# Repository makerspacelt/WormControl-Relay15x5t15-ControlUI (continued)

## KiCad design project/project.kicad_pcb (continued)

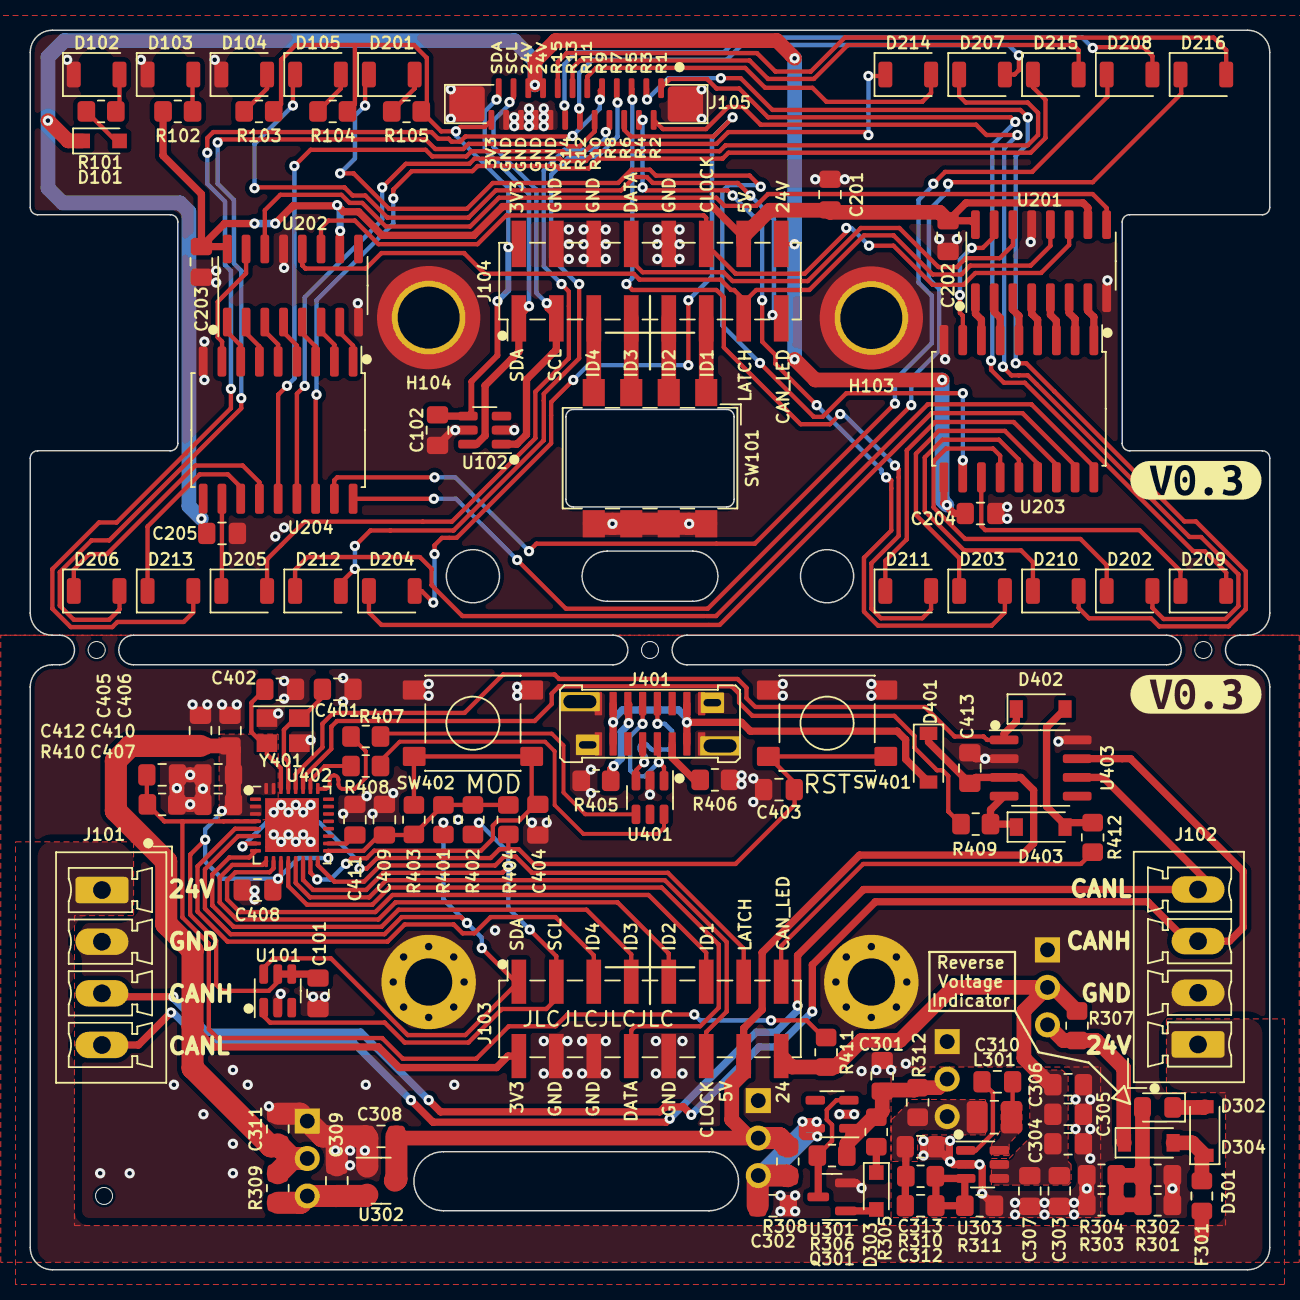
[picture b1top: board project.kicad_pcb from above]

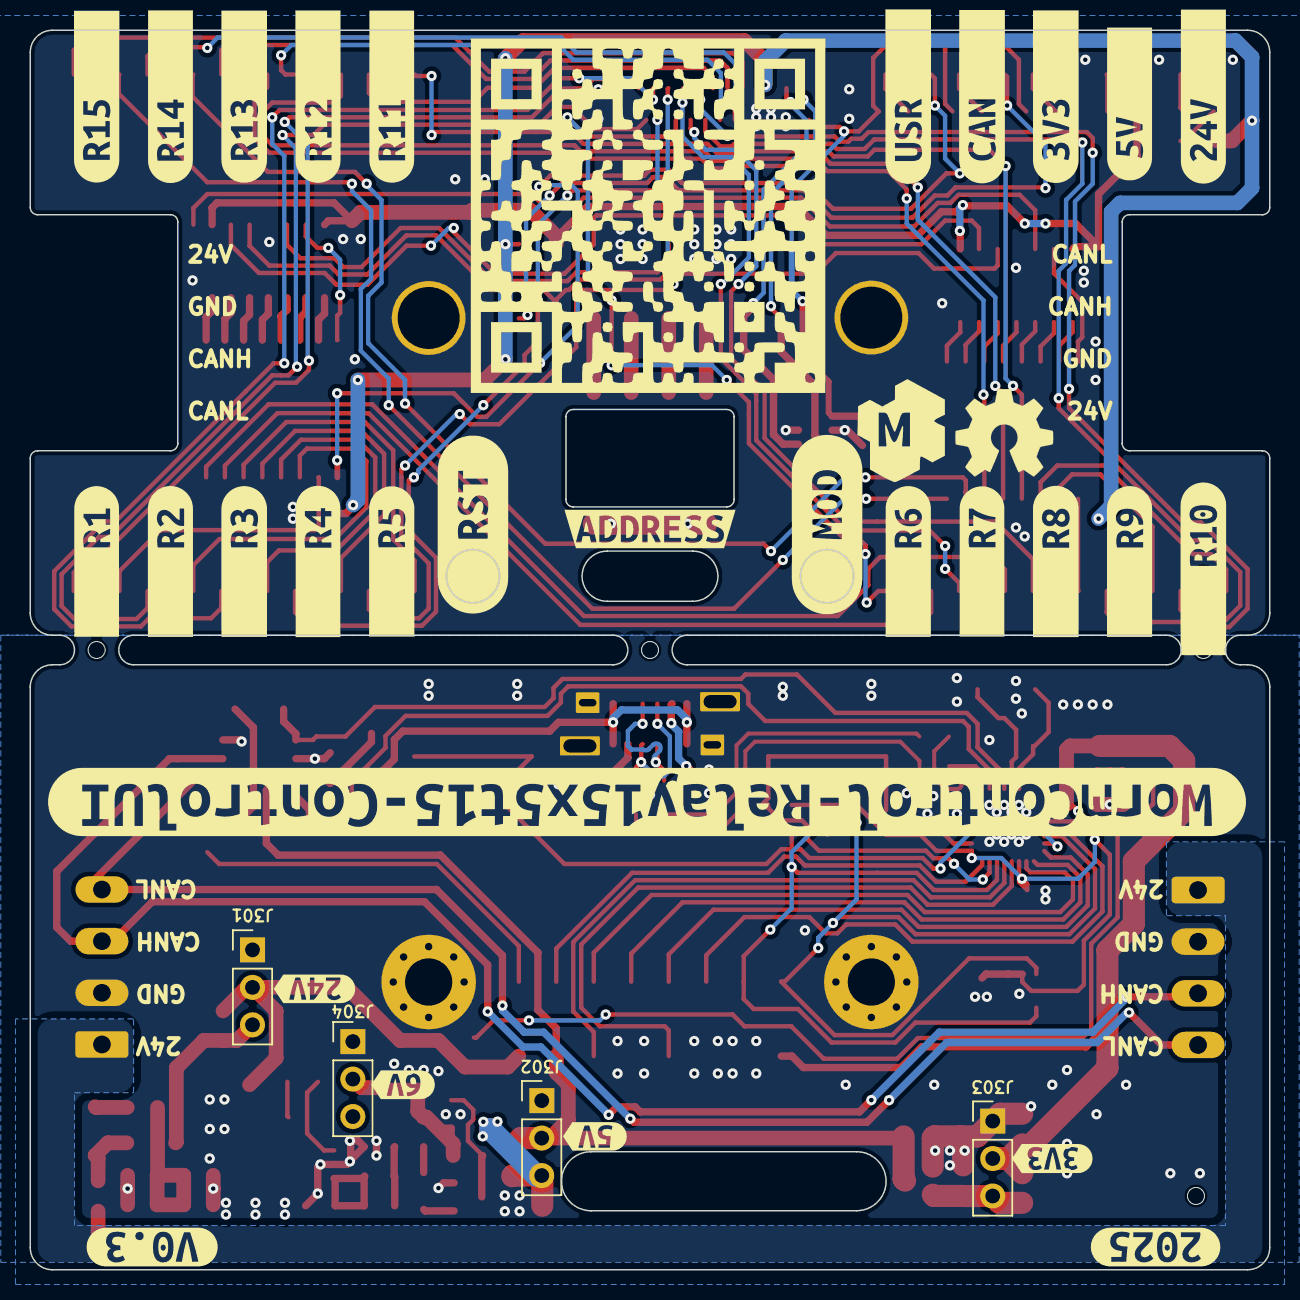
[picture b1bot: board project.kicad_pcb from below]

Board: 4 copper layers, 84.0 x 84.0 mm, 157 parts (36 on the bottom side), 118 nets.

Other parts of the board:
kibuzzard-68F6C7D9: G***; kibuzzard-68F6C7D9
kibuzzard-68F6C8CD: G***; kibuzzard-68F6C8CD
kibuzzard-68F6C9D1: G***; kibuzzard-68F6C9D1
kibuzzard-68F6C9D9: G***; kibuzzard-68F6C9D9
kibuzzard-68F6C81E: G***; kibuzzard-68F6C81E
kibuzzard-68F6C83B: G***; kibuzzard-68F6C83B
kibuzzard-68F6C776: G***; kibuzzard-68F6C776
kibuzzard-68F6C793: G***; kibuzzard-68F6C793
kibuzzard-67993A27: G***; kibuzzard-67993A27
kibuzzard-679934A0: G***; kibuzzard-679934A0
kibuzzard-679934B0: G***; kibuzzard-679934B0
kibuzzard-679934DC: G***; kibuzzard-679934DC
kibuzzard-679934EA: G***; kibuzzard-679934EA
kibuzzard-679935A9: G***; kibuzzard-679935A9
kibuzzard-679935B4: G***; kibuzzard-679935B4
kibuzzard-679935C1: G***; kibuzzard-679935C1
kibuzzard-6799352B: G***; kibuzzard-6799352B
kibuzzard-6799357E: G***; kibuzzard-6799357E
kibuzzard-6799359C: G***; kibuzzard-6799359C
kibuzzard-6799365E: G***; kibuzzard-6799365E
kibuzzard-67993413: G***; kibuzzard-67993413
kibuzzard-67993427: G***; kibuzzard-67993427
kibuzzard-67993436: G***; kibuzzard-67993436
kibuzzard-67993449: G***; kibuzzard-67993449
kibuzzard-67993459: G***; kibuzzard-67993459
kibuzzard-67993507: G***; kibuzzard-67993507
kibuzzard-67993514: G***; kibuzzard-67993514
kibuzzard-67993518: G***; kibuzzard-67993518
kibuzzard-67993537: G***; kibuzzard-67993537
kibuzzard-67993543: G***; kibuzzard-67993543
kibuzzard-67993570: G***; kibuzzard-67993570
kibuzzard-67993590: G***; kibuzzard-67993590

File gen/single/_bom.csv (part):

"Row","Description","Part","References","Value","Footprint","Quantity Per PCB","Status","Datasheet","lcsc#","jlc-part-type","alt#"
"1","Heatsink","Heatsink","BOM101,BOM102","1x4 screw plug","","2"," ","https://www.lcsc.com/datasheet/lcsc_datasheet_2309070925_DEG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","C7603442","E",""
"2","Unpolarized capacitor","C","C401,C402","10p","C_0805_2012Metric_Pad1.18x1.45mm_HandSolder","2"," ","https://www.lcsc.com/datasheet/lcsc_datasheet_2304140030_Sam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","C1634","B",""
"3","Unpolarized capacitor","C","C312","100p","C_0805_2012Metric_Pad1.18x1.45mm_HandSolder","1"," ","https://www.lcsc.com/datasheet/lcsc_datasheet_2304140030_Sam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","C1790","B",""
"4","Unpolarized capacitor","C","C101,C102,C202,C203,C307,C310,C403,C404,C407,C408,C409,C410,C411,C412,C413","100n","C_0805_2012Metric_Pad1.18x1.45mm_HandSolder","15"," ","https://www.lcsc.com/datasheet/lcsc_datasheet_2304140030_Sam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","C28233","B",""
"5","Unpolarized capacitor","C","C406","1u","C_0805_2012Metric_Pad1.18x1.45mm_HandSolder","1"," ","https://www.lcsc.com/datasheet/lcsc_datasheet_2304140030_Sam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","C28323","B",""
"6","Unpolarized capacitor","C","C204,C205,C301,C303,C304,C305,C306,C313","10u/50v","C_0805_2012Metric_Pad1.18x1.45mm_HandSolder","8"," ","https://www.lcsc.com/datasheet/lcsc_datasheet_2411041759_Mur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","C440198","B",""
"7","Unpolarized capacitor","C","C201,C302,C308,C405","22u/25v","C_0805_2012Metric_Pad1.18x1.45mm_HandSolder","4"," ","https://www.lcsc.com/datasheet/lcsc_datasheet_2304140030_Sam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","C45783","B",""
"8","Unpolarized capacitor","C","C309,C311","47u/6V3","C_0805_2012Metric_Pad1.18x1.45mm_HandSolder","2"," ","https://www.lcsc.com/datasheet/lcsc_datasheet_2304140030_Sam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","C16780","B",""
"9","Zener diode","D_Zener","D101,D303","6V8","D_SOD-323_HandSoldering","2"," ","https://www.lcsc.com/datasheet/C123062.pdf","C123062","E",""
"10","Schottky diode","D_Schottky","D301,D304,D401,D402,D403","B5819W","D_SOD-123","5"," ","https://www.lcsc.com/datasheet/lcsc_datasheet_2304140030_Jia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","C8598","B",""
"11","Light emitting diode","LED","D302","BLUE","LED_0805_2012Metric_Pad1.15x1.40mm_HandSolder","1"," ","https://jlcpcb.com/api/file/downloadByFileSystemAccessId/855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","C2297","B",""
"12","Light emitting diode","LED","D102,D103,D104,D105,D201,D202,D203,D204,D205,D206,D207,D208,D209,D210,D211,D212,D213,D214,D215,D216","RED","LED_1206_3216Metric_ReverseMount","20"," ","https://www.lcsc.com/datasheet/lcsc_datasheet_2302091130_TOG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","C5356080","E",""
"13","Resettable fuse, polymeric positive temperature coefficient","Polyfuse","F301","250mA","Fuse_0805_2012Metric_Pad1.15x1.40mm_HandSolder","1"," ","https://wmsc.lcsc.com/wmsc/upload/file/pdf/v2/lcsc/240408162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","C22378353","E",""
"14","Generic connector, single row, 01x03, script generated (kicad-library-utils/schlib/autogen/connector/)","Conn_01x03","J301,J302,J303,J304","24V","PinHeader_1x03_P2.54mm_Vertical","4"," ","~","","-",""
"15","Generic screw terminal, single row, 01x04, script generated (kicad-library-utils/schlib/autogen/connector/)","Screw_Terminal_01x04","J101,J102","BUS","PhoenixContact_MCV_1,5_4-G-3.5_1x04_P3.50mm_Vertical","2"," ","https://www.lcsc.com/datasheet/lcsc_datasheet_2304140030_Nin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","C880556","E",""
"16","Generic connector, single row, 01x16, script generated (kicad-library-utils/schlib/autogen/connector/)","Conn_01x16","J103","Back","PinSocket_2x08_P2.54mm_Vertical_SMD","1"," ","https://wmsc.lcsc.com/wmsc/upload/file/pdf/v2/lcsc/230609101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","C3975153","E",""
"17","Generic connectable mounting pin connector, single row, 01x24, script generated (kicad-library-utils/schlib/autogen/connector/)","Conn_01x24_MountingPin","J105","FFC","AFC11-S24ICC-00","1"," ","https://www.lcsc.com/datasheet/lcsc_datasheet_2212161930_JUS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","C11075","E",""
"18","Generic connector, single row, 01x16, script generated (kicad-library-utils/schlib/autogen/connector/)","Conn_01x16","J104","Front","PinHeader_2x08_P2.54mm_Vertical_SMD","1"," ","https://wmsc.lcsc.com/wmsc/upload/file/pdf/v2/lcsc/220914173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","C5160782","E",""
"19","USB 2.0-only Type-C Receptacle connector","USB_C_Receptacle_USB2.0","J401","USB_C_Receptacle_USB2.0","USB_C_Receptacle_G-Switch_GT-USB-7082G","1"," ","https://www.lcsc.com/datasheet/lcsc_datasheet_2405271642_G-S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","C22383836","E",""
"20","Inductor","L","L301","3.3uH","L_1008_2520Metric_Pad1.43x2.20mm_HandSolder","1"," ","https://www.lcsc.com/datasheet/C5832373.pdf","C5832373","E",""
"21","NPN transistor, base/emitter/collector","Q_NPN_BEC","Q301","MMBT3904","SOT-23","1"," ","https://www.lcsc.com/datasheet/C20526.pdf","C20526","B",""
"22","Resistor","R","R307,R308,R309,R312","0R1","R_0805_2012Metric_Pad1.20x1.40mm_HandSolder","4"," ","https://www.lcsc.com/datasheet/lcsc_datasheet_2304140030_UNI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","C127687","E",""
"23","Resistor","R","R407,R408","22R","R_0805_2012Metric_Pad1.20x1.40mm_HandSolder","2"," ","~","C17561","B",""
"24","Resistor","R","R103,R104,R105,R301,R302,R303,R304,R401,R402,R403,R404,R405,R406,R409,R410,R412","4k7","R_0805_2012Metric_Pad1.20x1.40mm_HandSolder","16"," ","~","C17673","B",""
"25","Resistor","R","R102,R305,R306","10k","R_0805_2012Metric_Pad1.20x1.40mm_HandSolder","3"," ","~","C17414","B",""
"26","Resistor","R","R311","22k","R_0805_2012Metric_Pad1.20x1.40mm_HandSolder","1"," ","~","C17560","B",""
"27","Resistor","R","R101","47k","R_0805_2012Metric_Pad1.20x1.40mm_HandSolder","1"," ","~","C17713","B",""
"28","Resistor","R","R411","150k","R_0805_2012Metric_Pad1.20x1.40mm_HandSolder","1"," ","~","C17470","B",""
"29","Resistor","R","R310","200k","R_0805_2012Metric_Pad1.20x1.40mm_HandSolder","1"," ","~","C17539","B",""
"30","Push button switch, generic, two pins","SW_Push","SW401,SW402","15mm","SW_SPST_15","2"," ","https://www.lcsc.com/datasheet/lcsc_datasheet_2110120830_XKB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","C2885154","E",""
"31","4x DIP Switch, Single Pole Single Throw (SPST) switch, small symbol","SW_DIP_x04","SW101","SW_DIP_x04","SW_DIP_SPSTx04_Slide_6.2x11.16mm_P2.54mm","1"," ","https://www.lcsc.com/datasheet/lcsc_datasheet_2304140030_KAI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","C976366","E",""
"32","8-bit serial in/out Shift Register 3-State Outputs","74HC595","U201,U202","74HC595","SOIC-16_3.9x9.9mm_P1.27mm","2"," ","https://www.lcsc.com/datasheet/lcsc_datasheet_2407241044_Nex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","C5947","B",""
"33","Digital Temperature Sensor with I2C/SMBus Interface, +/-2° C, one-shot conversion, alert, SOT-23-6","TMP101","U101,U102","GX101","SOT-23-6","2"," ","https://www.lcsc.com/datasheet/lcsc_datasheet_2409280202_GXC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","C5441728","E",""
"34","300mA Low Dropout Voltage Regulator, Fixed Output 3.3V, SOT-23","APE8865N-33-HF-3","U302","JTD6206-3.3V","SOT-23","1"," ","https://www.lcsc.com/datasheet/C42443428.pdf","C5446","B","C42443428"
"35","300mA Low Dropout Voltage Regulator, Fixed Output 0.9V, SOT-23-5","TLV71209_SOT23-5","U301","LW6550A23E","SOT-23-5","1"," ","https://www.lcsc.com/datasheet/C20754712.pdf","C20754712","E",""
"36","1.2 A Simple Buck Regulator, 3-26V input, 1.5Mhz","AOZ1280CI","U303","ME3121AM6G","SOT-23-6","1"," ","https://m.huazhoucn.com/upFiles/common/2022/12/ME3121_Series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","C2932938","E",""
"37","Darlington Transistor Arrays, SOIC18/DIP18","ULN2803A","U203,U204","ULN2803A","SOIC-18W_7.5x11.6mm_P1.27mm","2"," ","https://www.lcsc.com/datasheet/lcsc_datasheet_2311091738_UMW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","C845537","E",""
"38","Very low capacitance ESD protection diode, 2 data-line, SOT-23-6","USBLC6-2SC6","U401","USBLC6-2SC6","SOT-23-6","1"," ","https://www.lcsc.com/datasheet/lcsc_datasheet_2311091738_UMW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","C2687116","E",""
"39","High-Speed CAN Transceiver, standby mode, split pin, SOIC-8","TJA1042T","U403","XL1050","SOIC-8_3.9x4.9mm_P1.27mm","1"," ","https://www.lcsc.com/datasheet/lcsc_datasheet_2309141025_XIN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","C609746","E",""
"40","esp32-C3FH4X 4MB flash QFN32-1EP 5x5mm EP3.7x3.7mm","esp32-C3FH4X","U402","esp32-C3FH4X","QFN-32-1EP_5x5mm_P0.5mm_EP3.65x3.65mm","1"," ","https://www.espressif.com/sites/default/files/documentation/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","C2858491","E",""
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
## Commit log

2024-12-16 initial draft
2024-12-16 routing somewhat done
2024-12-18 fixing silk and bom and generating prod/doc files
2024-12-19 bom fixes
2024-12-20 fixing stencil for post footprint
2025-01-06 adding some 3d models
2025-01-06 adding buttons 3d models
2025-01-07 changing gerber file naming for compatibility
2025-01-07 adding screw post 3d model
2025-01-07 moving addr hole from footprint to board
2025-01-07 adjusting hole sizes and adding qfn model
2025-01-07 replacing connector and fixing models
2025-01-28 few fixes and bumping up version
    * reordering id bits
    * moving silkscreen around
    * adding hole in the center tab
2025-10-21 improvements for next prototype
    * buck makes 6v now
    * using LDO for 5v with over voltage disable
    * using LDO for 3v3
    * adding zener to 24v led to stop it from glowing from 5v USB
    * added 0.2mm heigt for USB port hole
    * both buttons now 15mm height
2025-10-31 adding threded posts to bom/pos
